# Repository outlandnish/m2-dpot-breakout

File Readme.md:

# Xbox Trigger Breakout for M2

This breakout board for the Macchina M2 let's you actuate Xbox Adaptive Controller left and right triggers using 3.5mm audio cables.

You will need:

* 4 channel 3.5mm headphone jacks - 2
* MCP4261 two channel digital potentiometer - 1
* 10 pin, 2mm pitch male headers - 2

Source code for the project [available here](https://github.com/outlandnish/m2-xbox-controller)

You can find a writeup for the project [here](https://www.notion.so/outlandnish/Play-Racing-Sims-with-Your-Car-3ef501bde46e4a8b9595280c3b2e59eb)

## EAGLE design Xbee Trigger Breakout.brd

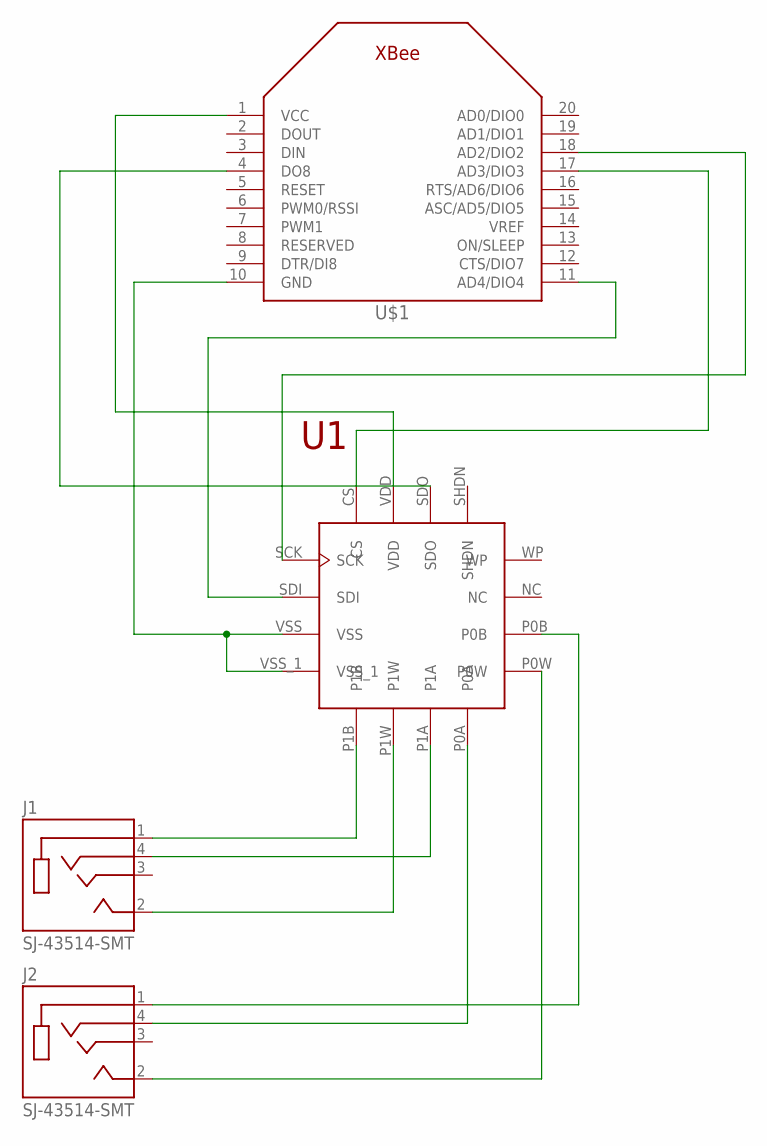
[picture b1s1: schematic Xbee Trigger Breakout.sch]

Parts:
J1, J2: SJ-43514-SMT; CUI_SJ-43514-SMT
U1: MCP4261; 2CH_DIGITAL_POT_QFN
U$1: XBEE

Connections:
GND: U1.VSS, U1.VSS_1, U$1.10 (GND)
unnamed: J1.1 (SLEEVE), U1.P1B
unnamed: J1.4 (RING2), U1.P1A
unnamed: J1.2 (TIP), U1.P1W
unnamed: J2.4 (RING2), U1.P0A
unnamed: J2.1 (SLEEVE), U1.P0B
unnamed: J2.2 (TIP), U1.P0W
unnamed: U1.SCK, U$1.18 (AD2/DIO2)
unnamed: U1.CS, U$1.17 (AD3/DIO3)
unnamed: U1.SDO, U$1.4 (DO8)
unnamed: U1.SDI, U$1.11 (AD4/DIO4)
VCC: U1.VDD, U$1.1 (VCC)

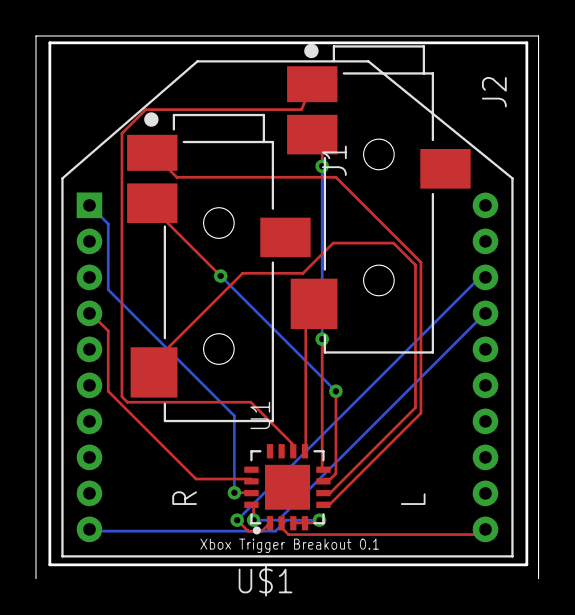
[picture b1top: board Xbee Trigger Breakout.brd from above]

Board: 2 copper layers, 27.8 x 30.0 mm, 4 parts (0 on the bottom side), 12 nets.

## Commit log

2019-09-14 formatting
